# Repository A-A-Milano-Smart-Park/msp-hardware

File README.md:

# Milano Smart Park Hardware

Hardware PCB files for the ESP32-based Milano Smart Park project

## Note: The PCB v7 files are old and deprecated. New design files need to be made to better represent the current state of the project!

- ESP32-DevkitC with ESP32-WROVER-B module with attached:

	- OLED Display SH1106 1.3" 128X64 (IIC)
	- SD Card Module
 	- SIM800L 2G Modem (Serial) 	
	- Adafruit's BME680 sensor (IIC)
	- Plantower's PMS5003 Air Quality sensor (Serial)
	- seeed's Grove Multichannel Gas Sensor MiCS-6814 v1.0 (IIC) (With custom modifications)
	
### Quick schematic of the ESP32 /w WROVER-B devkit:

	                                _____________________
	                               |                     |
	                             o-|-3V3             GND-|-o
	                             o-|-EN           GPIO23-|-o --- MOSI SDCARD
	                             o-|-VP(GPIO36)   GPIO22-|-o --- IIC SCL
	                             o-|-VN(GPIO39)(GPIO1)TX-|-o (UART0 debug)
	                             o-|-GPIO34    (GPIO3)RX-|-o (UART0 debug)
	                             o-|-GPIO35       GPIO21-|-o --- IIC SDA
	                  (ADC1) --- o-|-GPIO32          GND-|-o
	                             o-|-GPIO33       GPIO19-|-o --- MISO SDCARD
	                             o-|-GPIO25       GPIO18-|-o --- SCK SDCARD
	                             o-|-GPIO26       GPIO5 -|-o --- CS SDCARD
	                             o-|-GPIO27       GPIO17-|-x reserved, don't use!
	      (UART2) PMS5003 RX --- o-|-GPIO14       GPIO16-|-x reserved, don't use!
	      (UART2) PMS5003 TX --- o-|-GPIO12       GPIO4 -|-o --- | diode --- SIM800L RST
	             SIM800L GND --- o-|-GND          GPIO0 -|-o
	 (UART1) SIM800L SIM_RXD --- o-|-GPIO13       GPIO2 -|-o
	        reserved, don't use! x-|-D2(SD)       GPIO15-|-o --- SIM800L SIM_TXD (UART1)
	        reserved, don't use! x-|-D3(SD)       (SD)D1-|-x reserved, don't use!
	        reserved, don't use! x-|-CMD(SD)      (SD)D0-|-x reserved, don't use!
	                     VCC --- o-|-5V          (SD)CLK-|-x reserved, don't use!
	                               |                     |
	                               |       _______       |
	                               |      |       |      |
	                               |      |       |      |
	                               |______|       |______|
	                                      |_______|

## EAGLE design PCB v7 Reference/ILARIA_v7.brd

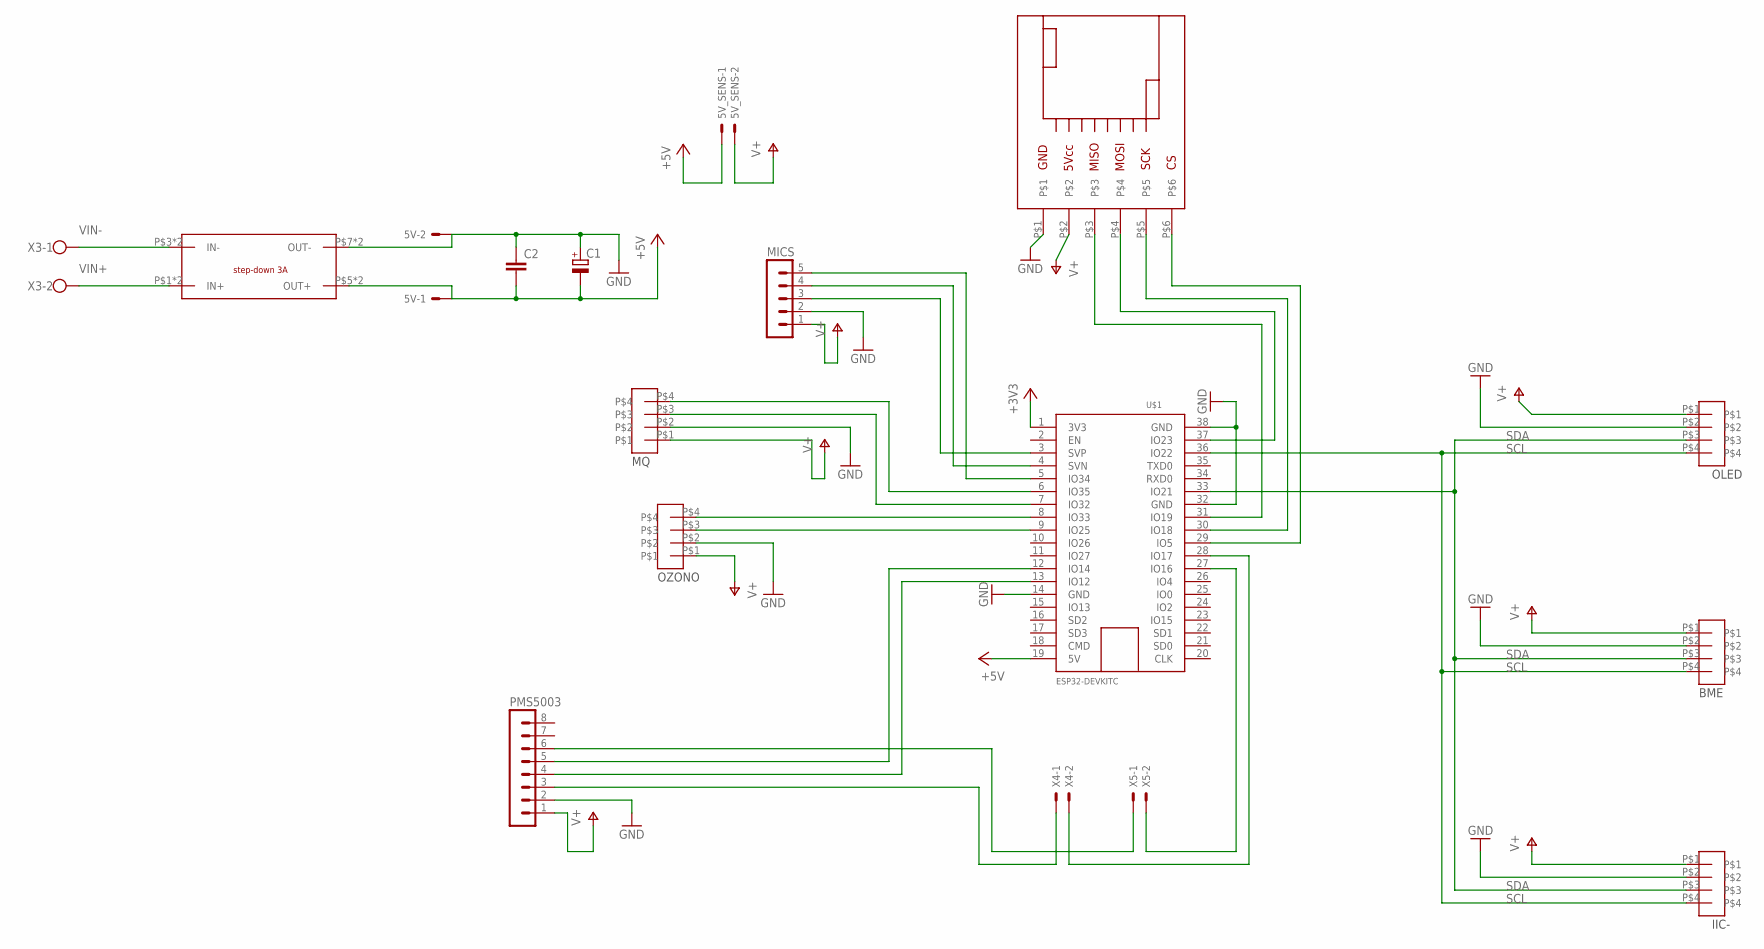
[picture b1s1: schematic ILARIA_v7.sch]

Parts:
5V: 22-27-2021-02; 6410-02
5V_SENS: 22-23-2021
AN-1: JST_4PIN_20
C1: CPOL-EUE2.5-7; E2,5-7
C2: C-EU050-025X075; C050-025X075
MICS: MA05-1
OLED: OLED; JST_4PIN_20
PMS5003: MA08-1
U$1: ESP32DEVKITC; ESP32-DEVKITC
U$2: USD_CARD; USDCARD_BOARD
U$3: STEP_DOWN; STEP_DOWN_MODULE
U$4, U$5, U$6: JST_4PIN_20
X3: W237-102
X4, X5: 87758-0216

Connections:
+3V3: U$1.1 (3V3)
+5V: 5V.1, 5V_SENS.1, C1.-, C2.2, U$1.19 (5V), U$3.P$5 (OUT+), U$3.P$6 (OUT+)
GND: 5V.2, AN-1.P$2, C1.+, C2.1, MICS.2, OLED.P$2, PMS5003.2, U$1.14 (GND), U$1.32 (GND), U$1.38 (GND), U$2.P$1, U$3.P$7 (OUT-), U$3.P$8 (OUT-), U$4.P$2, U$5.P$2, U$6.P$2
unnamed: U$1.31 (IO19), U$2.P$3
unnamed: U$1.37 (IO23), U$2.P$4
unnamed: U$1.30 (IO18), U$2.P$5
unnamed: U$1.29 (IO5), U$2.P$6
unnamed: MICS.4, U$1.4 (SVN)
unnamed: MICS.3, U$1.3 (SVP)
unnamed: MICS.5, U$1.5 (IO34)
unnamed: U$1.7 (IO32), U$4.P$3
unnamed: U$1.6 (IO35), U$4.P$4
unnamed: PMS5003.5, U$1.12 (IO14)
unnamed: PMS5003.4, U$1.13 (IO12)
unnamed: PMS5003.3, X4.1
unnamed: U$1.28 (IO17), X4.2
unnamed: U$1.27 (IO16), X5.2
unnamed: PMS5003.6, X5.1
SCL: AN-1.P$4, OLED.P$4, U$1.36 (IO22), U$5.P$4, U$6.P$4
SDA: AN-1.P$3, OLED.P$3, U$1.33 (IO21), U$5.P$3, U$6.P$3
V+: 5V_SENS.2, AN-1.P$1, MICS.1, OLED.P$1, PMS5003.1, U$2.P$2, U$4.P$1, U$5.P$1, U$6.P$1
VIN+: U$3.P$1 (IN+), U$3.P$2 (IN+), X3.2
VIN-: U$3.P$3 (IN-), U$3.P$4 (IN-), X3.1

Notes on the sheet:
OLED
BME
IIC-
OZONO

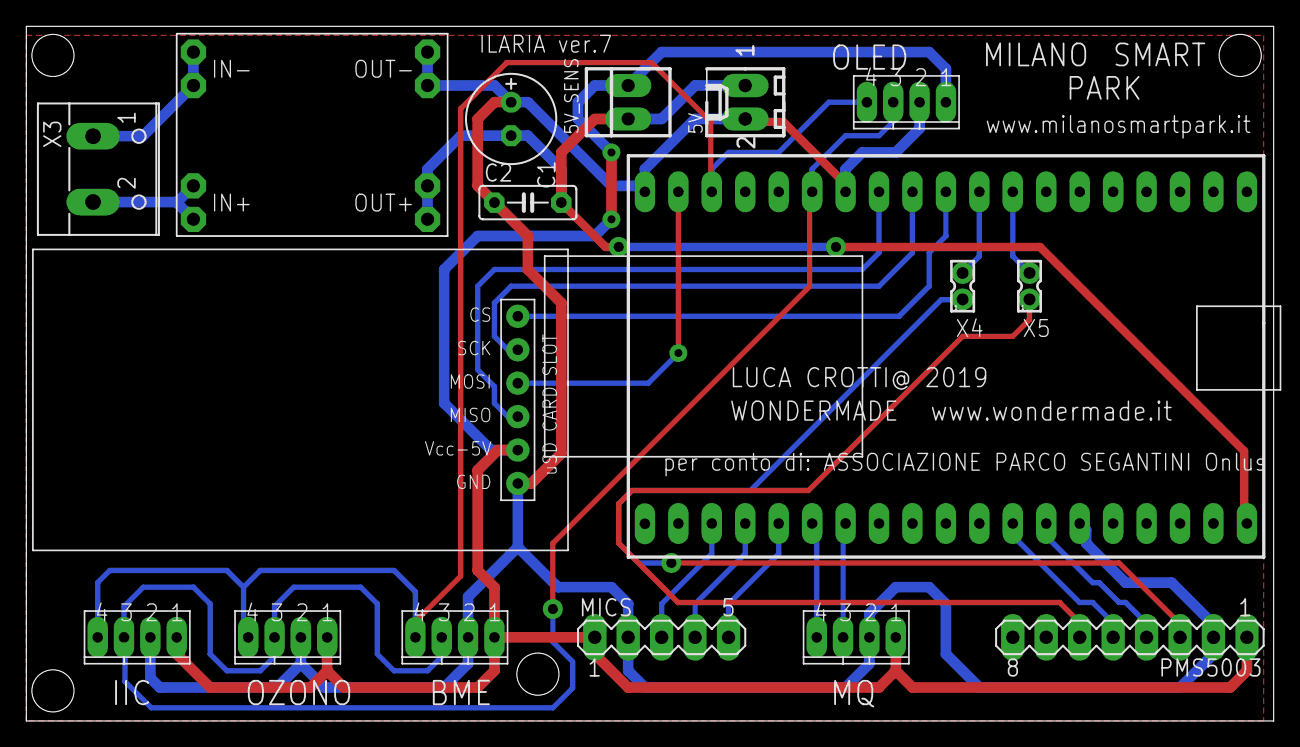
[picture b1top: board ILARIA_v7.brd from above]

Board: 2 copper layers, 94.6 x 52.6 mm, 17 parts (0 on the bottom side), 22 nets.

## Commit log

2020-12-11 Added old PCB v7 gerber files
2020-12-12 Moved image files
